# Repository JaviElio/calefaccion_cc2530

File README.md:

# calefaccion_cc2530
CC2531 ptvo firmware

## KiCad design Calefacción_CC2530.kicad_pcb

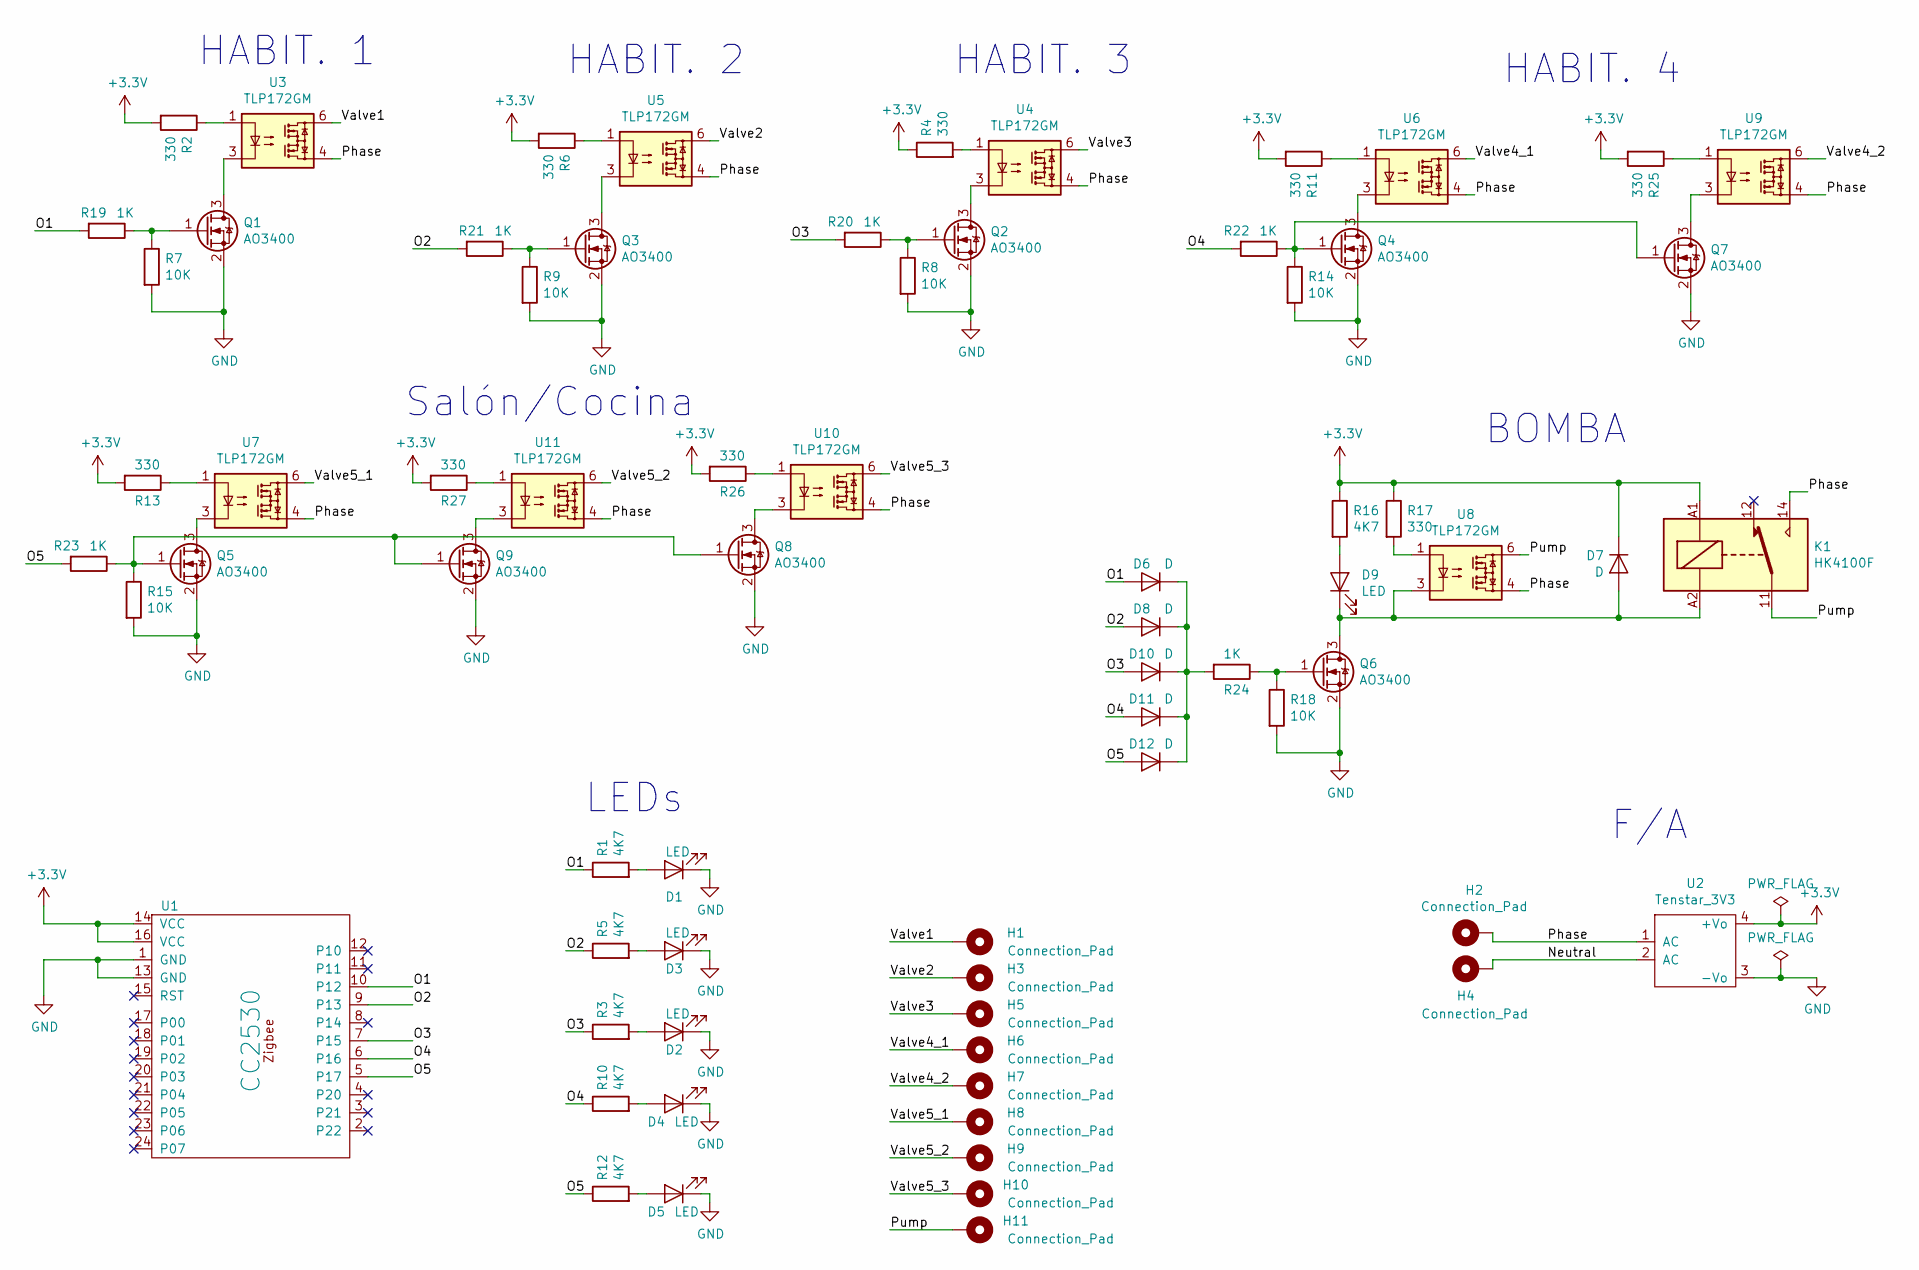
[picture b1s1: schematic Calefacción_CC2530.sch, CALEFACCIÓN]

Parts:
D1, D2, D3, D4, D5, D9: LED; LED_0805_2012Metric_Pad1.15x1.40mm_HandSolder
D6, D7, D8, D10, D11, D12: D; D_DO-35_SOD27_P7.62mm_Horizontal
H1, H3, H5, H6, H7, H8, H9, H10: Connection_Pad; TestPoint_THTPad_D2.0mm_Drill1.0mm
H2, H4, H11: Connection_Pad; TestPoint_THTPad_D4.0mm_Drill2.0mm
K1: HK4100F
Q1, Q2, Q3, Q4, Q5, Q6, Q7, Q8, Q9: AO3400; SOT-23_Handsoldering
R1, R3, R5, R10, R12, R16: 4K7; R_0805_2012Metric_Pad1.15x1.40mm_HandSolder
R2, R4, R6, R11, R13, R17, R25, R26, R27: 330; R_0805_2012Metric_Pad1.15x1.40mm_HandSolder
R7, R8, R9, R14, R15, R18: 10K; R_0805_2012Metric_Pad1.15x1.40mm_HandSolder
R19, R20, R21, R22, R23, R24: 1K; R_0805_2012Metric_Pad1.15x1.40mm_HandSolder
U1: CC2530; CC2530_Module
U2: Tenstar_3V3; Tenstar_PS_3V3
U3, U4, U5, U6, U7, U8, U9, U10, U11: TLP172GM; MFSOP6-4_4.4x3.6mm_P1.27mm

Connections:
+3V3: D7.1 (K), K1.A1, R2.2, R4.1, R6.2, R11.2, R13.2, R16.1, R17.1, R25.2, R26.2, R27.2, U1.14 (VCC), U1.16 (VCC), U2.4 (+Vo)
/Neutral: H4.1, U2.2 (AC)
/O1: D6.2 (A), R1.1, R19.2, U1.10 (P12)
/O2: D8.2 (A), R5.1, R21.2, U1.9 (P13)
/O3: D10.2 (A), R3.1, R20.2, U1.7 (P15)
/O4: D11.2 (A), R10.1, R22.2, U1.6 (P16)
/O5: D12.2 (A), R12.1, R23.2, U1.5 (P17)
/Phase: H2.1, K1.14, U2.1 (AC), U3.4, U4.4, U5.4, U6.4, U7.4, U8.4, U9.4, U10.4, U11.4
/Pump: H11.1, K1.11, U8.6
/Valve1: H1.1, U3.6
/Valve2: H3.1, U5.6
/Valve3: H5.1, U4.6
/Valve4_1: H6.1, U6.6
/Valve4_2: H7.1, U9.6
/Valve5_1: H8.1, U7.6
/Valve5_2: H9.1, U11.6
/Valve5_3: H10.1, U10.6
GND: D1.1 (K), D2.1 (K), D3.1 (K), D4.1 (K), D5.1 (K), Q1.2 (S), Q2.2 (S), Q3.2 (S), Q4.2 (S), Q5.2 (S), Q6.2 (S), Q7.2 (S), Q8.2 (S), Q9.2 (S), R7.2, R8.2, R9.2, R14.2, R15.2, R18.2, U1.1 (GND), U1.13 (GND), U2.3 (-Vo)
unnamed: D1.2 (A), R1.2
unnamed: D2.2 (A), R3.2
unnamed: D3.2 (A), R5.2
unnamed: D4.2 (A), R10.2
unnamed: D5.2 (A), R12.2
unnamed: D7.2 (A), D9.1 (K), K1.A2, Q6.3 (D), U8.3
unnamed: D9.2 (A), R16.2
unnamed: D6.1 (K), D8.1 (K), D10.1 (K), D11.1 (K), D12.1 (K), R24.2
unnamed: Q1.1 (G), R7.1, R19.1
unnamed: Q1.3 (D), U3.3
unnamed: Q2.1 (G), R8.1, R20.1
unnamed: Q2.3 (D), U4.3
unnamed: Q3.1 (G), R9.1, R21.1
unnamed: Q3.3 (D), U5.3
unnamed: Q4.1 (G), Q7.1 (G), R14.1, R22.1
unnamed: Q4.3 (D), U6.3
unnamed: Q5.1 (G), Q8.1 (G), Q9.1 (G), R15.1, R23.1
unnamed: Q5.3 (D), U7.3
unnamed: Q6.1 (G), R18.1, R24.1
unnamed: Q7.3 (D), U9.3
unnamed: Q8.3 (D), U10.3
unnamed: Q9.3 (D), U11.3
unnamed: R2.1, U3.1
unnamed: R4.2, U4.1
unnamed: R6.1, U5.1
unnamed: R11.1, U6.1
unnamed: R13.1, U7.1
unnamed: R17.2, U8.1
unnamed: R25.1, U9.1
unnamed: R26.1, U10.1
unnamed: R27.1, U11.1

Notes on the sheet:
BOMBA
HABIT. 1
HABIT. 2
HABIT. 3
HABIT. 4
Salón/Cocina
LEDs
F/A

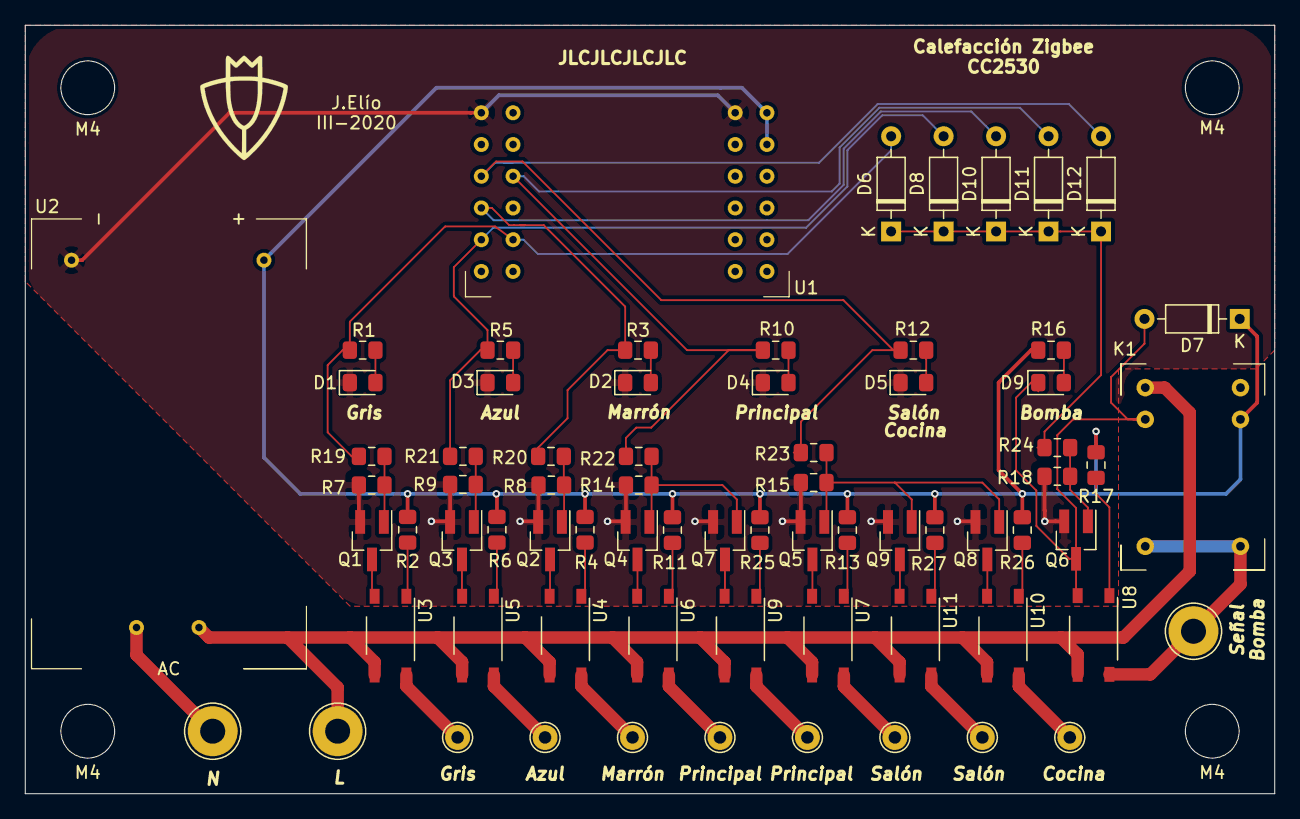
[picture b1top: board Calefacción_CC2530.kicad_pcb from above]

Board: 2 copper layers, 100.0 x 61.5 mm, 75 parts (0 on the bottom side), 49 nets.

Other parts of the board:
M4, M4#2, M4#3, M4#4: MountingHole_4.3mm_M4

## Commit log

2020-05-19 first upload
